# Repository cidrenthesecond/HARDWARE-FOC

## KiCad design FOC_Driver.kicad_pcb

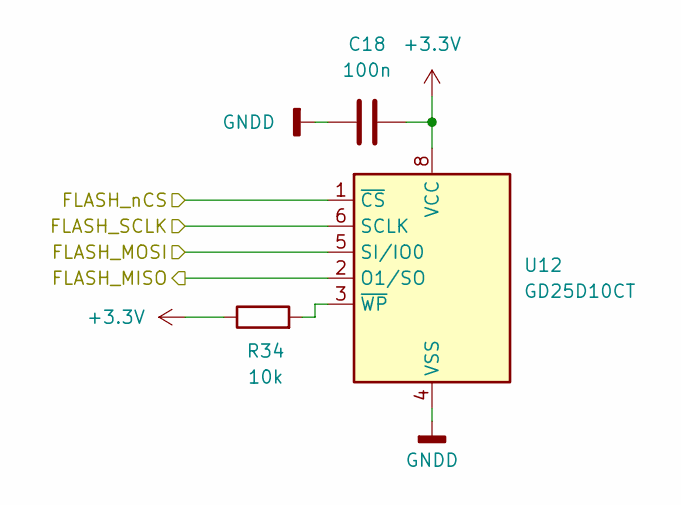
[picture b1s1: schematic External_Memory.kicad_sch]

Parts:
C18: 100n; C_0805_Private
R34: 10k; R_0805_Private
U12: GD25D10CT; JEITA_SOIC-8_3.9x4.9mm_P1.27mm

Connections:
+3.3V: C18.1, R34.1, U12.8 (VCC); also elsewhere on the board
/External_Memory/FLASH_MISO: U12.2 (O1/SO); also elsewhere on the board
/External_Memory/FLASH_MOSI: U12.5 (SI/IO0); also elsewhere on the board
/External_Memory/FLASH_SCLK: U12.6 (SCLK); also elsewhere on the board
/External_Memory/FLASH_nCS: U12.1 (~CS); also elsewhere on the board
GNDD: C18.2, U12.4 (VSS); also elsewhere on the board
unnamed: R34.2, U12.3 (~WP)

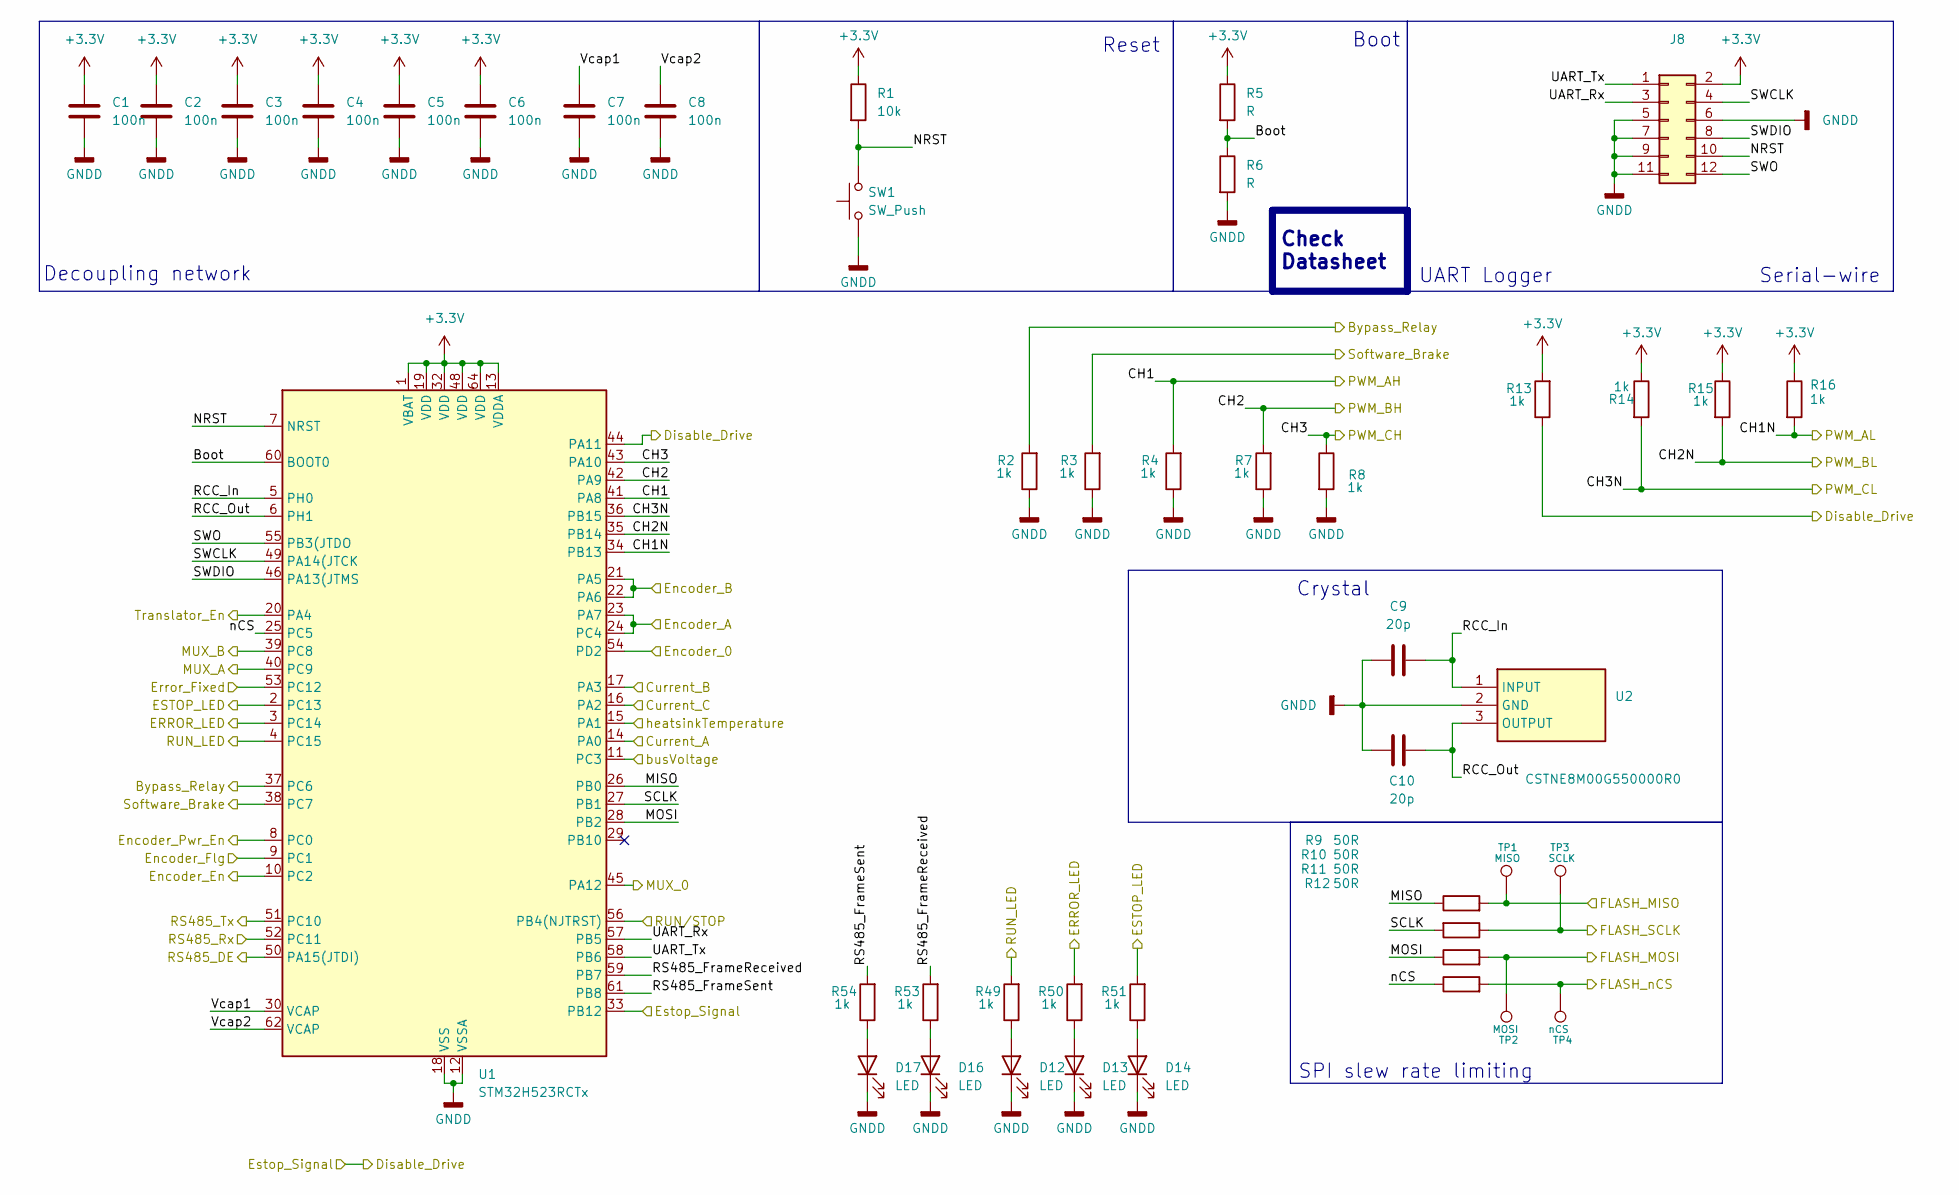
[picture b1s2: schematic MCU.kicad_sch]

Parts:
C1, C2, C3, C4, C5, C6, C7, C8: 100n; C_0805_Private
C9, C10: 20p; C_0805_Private
D12, D13, D14, D16, D17: LED; LED_0805_Private
J8: Conn_02x06_Odd_Even; PinHeader_2x06_P2.54mm_Vertical
R1: 10k; R_0805_Private
R2, R3, R4, R7, R8, R13, R14, R15, R16, R49, R50, R51, R53, R54: 1k; R_0805_Private
R5, R6: R; R_0805_Private
R9, R10, R11, R12: 50R; R_0805_Private
SW1: SW_Push; SW_PUSH_6mm_H5mm
TP1: MISO; TestPoint_Pad_D1.0mm
TP2: MOSI; TestPoint_Pad_D1.0mm
TP3: SCLK; TestPoint_Pad_D1.0mm
TP4: nCS; TestPoint_Pad_D1.0mm
U1: STM32H523RCTx; LQFP-64_10x10mm_P0.5mm
U2: CSTNE8M00G550000R0; CSTNE16M0V530000R0; Manufacturer_Part_Number CSTNE8M00G550000R0

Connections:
+3.3V: C1.1, C2.1, C3.1, C4.1, C5.1, C6.1, J8.2, R1.1, R5.1, R13.2, R14.1, R15.1, R16.1, U1.1 (VBAT), U1.13 (VDDA), U1.19 (VDD), U1.32 (VDD), U1.48 (VDD), U1.64 (VDD); also elsewhere on the board
/Connectors/BypassRelay: R2.2, U1.37 (PC6); also elsewhere on the board
/Connectors/Current_A: U1.14 (PA0); also elsewhere on the board
/Connectors/Current_B: U1.17 (PA3); also elsewhere on the board
/Connectors/Current_C: U1.16 (PA2); also elsewhere on the board
/Connectors/Disable_Drive: R13.1, U1.33 (PB12), U1.44 (PA11); also elsewhere on the board
/Connectors/SoftwareBrake: R3.2, U1.38 (PC7); also elsewhere on the board
/Connectors/busVoltage: U1.11 (PC3); also elsewhere on the board
/Connectors/heatsinkTemperature: U1.15 (PA1); also elsewhere on the board
/Encoder/Encoder_0: U1.54 (PD2); also elsewhere on the board
/Encoder/Encoder_A: U1.23 (PA7), U1.24 (PC4); also elsewhere on the board
/Encoder/Encoder_B: U1.21 (PA5), U1.22 (PA6); also elsewhere on the board
/Encoder/Encoder_En: U1.10 (PC2); also elsewhere on the board
/Encoder/Encoder_Flg: U1.9 (PC1); also elsewhere on the board
/Encoder/Encoder_Pwr_En: U1.8 (PC0); also elsewhere on the board
/Encoder/MUX_0: U1.45 (PA12); also elsewhere on the board
/Encoder/MUX_A: U1.40 (PC9); also elsewhere on the board
/Encoder/MUX_B: U1.39 (PC8); also elsewhere on the board
/Encoder/Translator_En: U1.20 (PA4); also elsewhere on the board
/External_Memory/FLASH_MISO: R9.2, TP1.1 (1_1); also elsewhere on the board
/External_Memory/FLASH_MOSI: R11.2, TP2.1 (1_1); also elsewhere on the board
/External_Memory/FLASH_SCLK: R10.1, TP3.1 (1_1); also elsewhere on the board
/External_Memory/FLASH_nCS: R12.2, TP4.1 (1_1); also elsewhere on the board
/MCU/Boot: R5.2, R6.1, U1.60 (BOOT0)
/MCU/CH1: R4.2, U1.41 (PA8); also elsewhere on the board
/MCU/CH1N: R16.2, U1.34 (PB13); also elsewhere on the board
/MCU/CH2: R7.2, U1.42 (PA9); also elsewhere on the board
/MCU/CH2N: R15.2, U1.35 (PB14); also elsewhere on the board
/MCU/CH3: R8.1, U1.43 (PA10); also elsewhere on the board
/MCU/CH3N: R14.2, U1.36 (PB15); also elsewhere on the board
/MCU/ERROR_LED: R50.2, U1.3 (PC14); also elsewhere on the board
/MCU/ESTOP_LED: R51.2, U1.2 (PC13); also elsewhere on the board
/MCU/MISO: R9.1, U1.26 (PB0)
/MCU/MOSI: R11.1, U1.28 (PB2)
/MCU/NRST: J8.10, R1.2, SW1.2, U1.7 (NRST)
/MCU/RCC_In: C9.2, U1.5 (PH0), U2.1 (INPUT)
/MCU/RCC_Out: C10.1, U1.6 (PH1), U2.3 (OUTPUT)
/MCU/RS485_DE: U1.50 (PA15(JTDI)); also elsewhere on the board
/MCU/RS485_FrameReceived: R53.2, U1.59 (PB7)
/MCU/RS485_FrameSent: R54.2, U1.61 (PB8)
/MCU/RS485_Rx: U1.52 (PC11); also elsewhere on the board
/MCU/RS485_Tx: U1.51 (PC10); also elsewhere on the board
/MCU/RUN_LED: R49.2, U1.4 (PC15); also elsewhere on the board
/MCU/SCLK: R10.2, U1.27 (PB1)
/MCU/SWCLK: J8.4, U1.49 (PA14(JTCK)
/MCU/SWDIO: J8.8, U1.46 (PA13(JTMS)
/MCU/SWO: J8.12, U1.55 (PB3(JTDO)
/MCU/UART_Rx: J8.3, U1.57 (PB5)
/MCU/UART_Tx: J8.1, U1.58 (PB6)
/MCU/Vcap1: C7.1, U1.30 (VCAP)
/MCU/Vcap2: C8.1, U1.62 (VCAP)
/MCU/nCS: R12.1, U1.25 (PC5)
Error_Fixed: U1.53 (PC12); also elsewhere on the board
GNDD: C1.2, C2.2, C3.2, C4.2, C5.2, C6.2, C7.2, C8.2, C9.1, C10.2, D12.1 (K), D13.1 (K), D14.1 (K), D16.1 (K), D17.1 (K), J8.5, J8.6, J8.7, J8.9, J8.11, R2.1, R3.1, R4.1, R6.2, R7.1, R8.2, SW1.1, U1.12 (VSSA), U1.18 (VSS), U1.31 (VSS), U1.47 (VSS), U1.63 (VSS), U2.2 (GND); also elsewhere on the board
unnamed: D12.2 (A), R49.1
unnamed: D13.2 (A), R50.1
unnamed: D14.2 (A), R51.1
unnamed: D16.2 (A), R53.1
unnamed: D17.2 (A), R54.1
RUN/STOP: U1.56 (PB4(NJTRST)); also elsewhere on the board

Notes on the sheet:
Crystal
SPI slew rate limiting
Check Datasheet
Decoupling network
Boot
UART Logger
Reset
Serial-wire

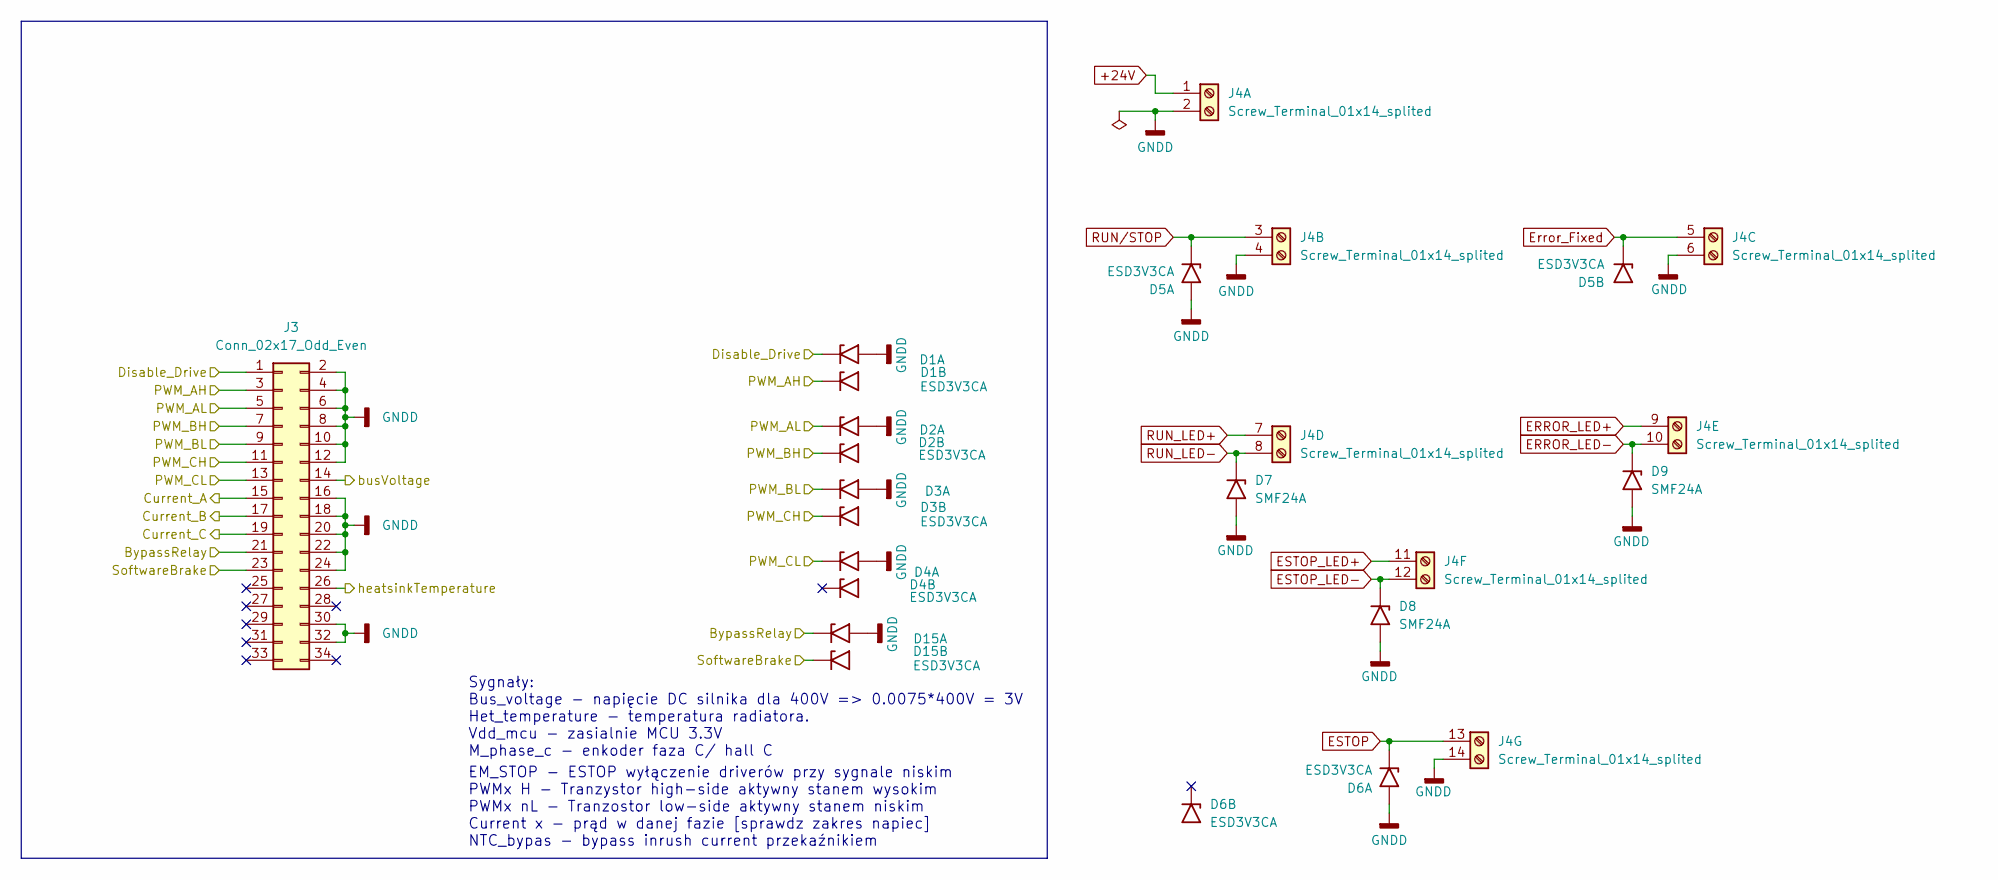
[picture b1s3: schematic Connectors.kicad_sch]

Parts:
D1, D2, D3, D4, D5, D6, D15: ESD3V3CA; SOT-23
D7, D8, D9: SMF24A; D_SMF_Private
J3: Conn_02x17_Odd_Even; IDC-Header_2x17_P2.54mm_Vertical
J4: Screw_Terminal_01x14_splited; TerminalBlock_Xinya_XY308-2.54-14P_1x14_P2.54mm_Horizontal

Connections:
/Connectors/BypassRelay: D15.1 (A1), J3.21; also elsewhere on the board
/Connectors/Current_A: J3.15; also elsewhere on the board
/Connectors/Current_B: J3.17; also elsewhere on the board
/Connectors/Current_C: J3.19; also elsewhere on the board
/Connectors/Disable_Drive: D1.1 (A1), J3.1; also elsewhere on the board
/Connectors/SoftwareBrake: D15.2 (A1), J3.23; also elsewhere on the board
/Connectors/busVoltage: J3.14; also elsewhere on the board
/Connectors/heatsinkTemperature: J3.26; also elsewhere on the board
/MCU/CH1: D1.2 (A1), J3.3; also elsewhere on the board
/MCU/CH1N: D2.1 (A1), J3.5; also elsewhere on the board
/MCU/CH2: D2.2 (A1), J3.7; also elsewhere on the board
/MCU/CH2N: D3.1 (A1), J3.9; also elsewhere on the board
/MCU/CH3: D3.2 (A1), J3.11; also elsewhere on the board
/MCU/CH3N: D4.1 (A1), J3.13; also elsewhere on the board
ERROR_LED-: D9.1 (A1), J4.10 (1); also elsewhere on the board
ESTOP: D6.1 (A1), J4.13 (Pin_1); also elsewhere on the board
ESTOP_LED-: D8.1 (A1), J4.12 (10); also elsewhere on the board
Error_Fixed: D5.2 (A1), J4.5 (Pin_1); also elsewhere on the board
GNDD: D1.3, D2.3, D3.3, D4.3, D5.3, D6.3, D7.2 (A2), D8.2 (A2), D9.2 (A2), D15.3, J3.2, J3.4, J3.6, J3.8, J3.10, J3.12, J3.16, J3.18, J3.20, J3.22, J3.24, J3.30, J3.32, J4.2, J4.4 (Pin_2), J4.6 (Pin_2), J4.14 (Pin_2); also elsewhere on the board
RUN_LED-: D7.1 (A1), J4.8 (Pin_2); also elsewhere on the board
RUN/STOP: D5.1 (A1), J4.3 (Pin_1); also elsewhere on the board

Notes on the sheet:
EM_STOP - ESTOP wyłączenie driverów przy sygnale niskim PWMx H - Tranzystor high-side aktywny stanem wysokim PWMx nL - Tranzostor low-side aktywny stanem niskim Current x - prąd w danej fazie [sprawdz zakres napiec] NTC_bypas - bypass inrush current przekaźnikiem
Sygnały: Bus_voltage - napięcie DC silnika dla 400V => 0.0075*400V = 3V Het_temperature - temperatura radiatora. Vdd_mcu - zasialnie MCU 3.3V M_phase_c - enkoder faza C/ hall C

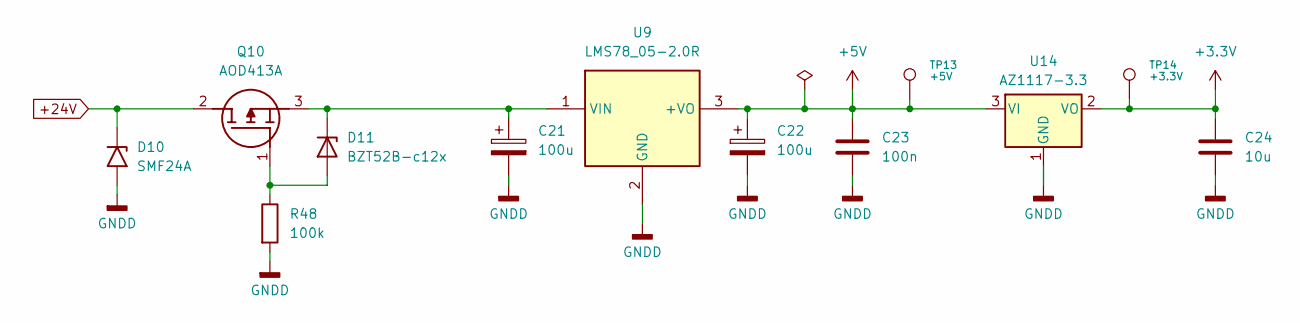
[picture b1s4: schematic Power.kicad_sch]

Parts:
C21, C22: 100u; CP_Radial_D8.0mm_P3.50mm
C23: 100n; C_0805_Private
C24: 10u; C_0805_Private
D10: SMF24A; D_SMF_Private
D11: BZT52B-c12x; D_SOD-123F_Private
Q10: AOD413A; Manufacturer_Part_Number AOD413A
R48: 100k; R_0805_Private
TP13: +5V; TestPoint_Pad_D1.0mm
TP14: +3.3V; TestPoint_Pad_D1.0mm
U9: LMS78_05-2.0R; LMS78_0520R; Manufacturer_Part_Number LMS78_05-2.0R
U14: AZ1117-3.3; SOT-223-3_TabPin2

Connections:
+3.3V: C24.2, TP14.1 (1_1), U14.2 (VO); also elsewhere on the board
+5V: C22.1, C23.2, TP13.1 (1_1), U9.3 (+VO), U14.3 (VI); also elsewhere on the board
GNDD: C21.2, C22.2, C23.1, C24.1, D10.2 (A2), R48.2, U9.2 (GND), U14.1 (GND); also elsewhere on the board
unnamed: D11.2 (A), Q10.1 (G), R48.1
unnamed: C21.1, D11.1 (K), Q10.3 (S), U9.1 (VIN)

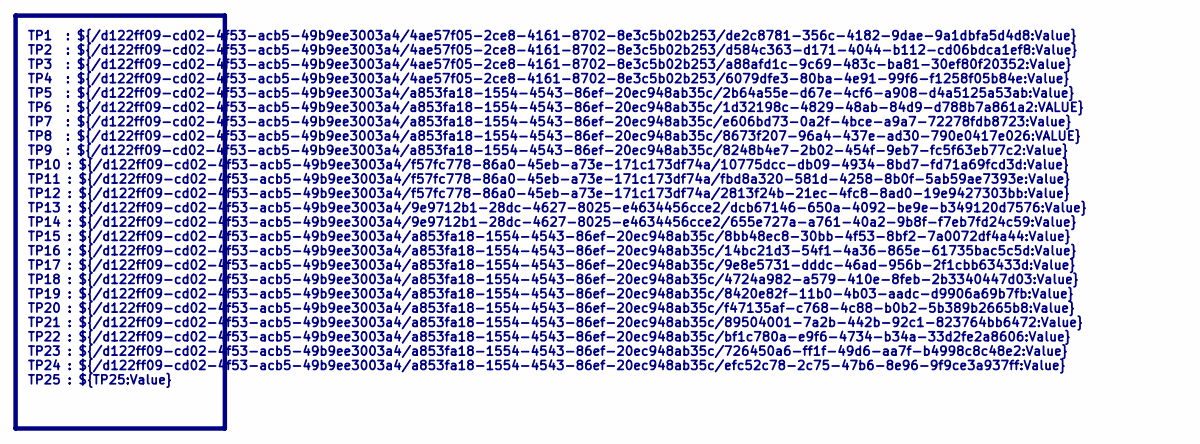
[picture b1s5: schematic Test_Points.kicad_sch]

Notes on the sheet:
TP1 : ${/d122ff09-cd02-4f53-acb5-49b9ee3003a4/4ae57f05-2ce8-4161-8702-8e3c5b02b253/de2c8781-356c-4182-9dae-9a1dbfa5d4d8:Value} TP2 : ${/d122ff09-cd02-4f53-acb5-49b9ee3003a4/4ae57f05-2ce8-4161-8702-8e3c5b02b253/d584c363-d171-4044-b112-cd06bdca1ef8:Value} TP3 : ${/d122ff09-cd02-4f53-acb5-49b9ee3003a4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

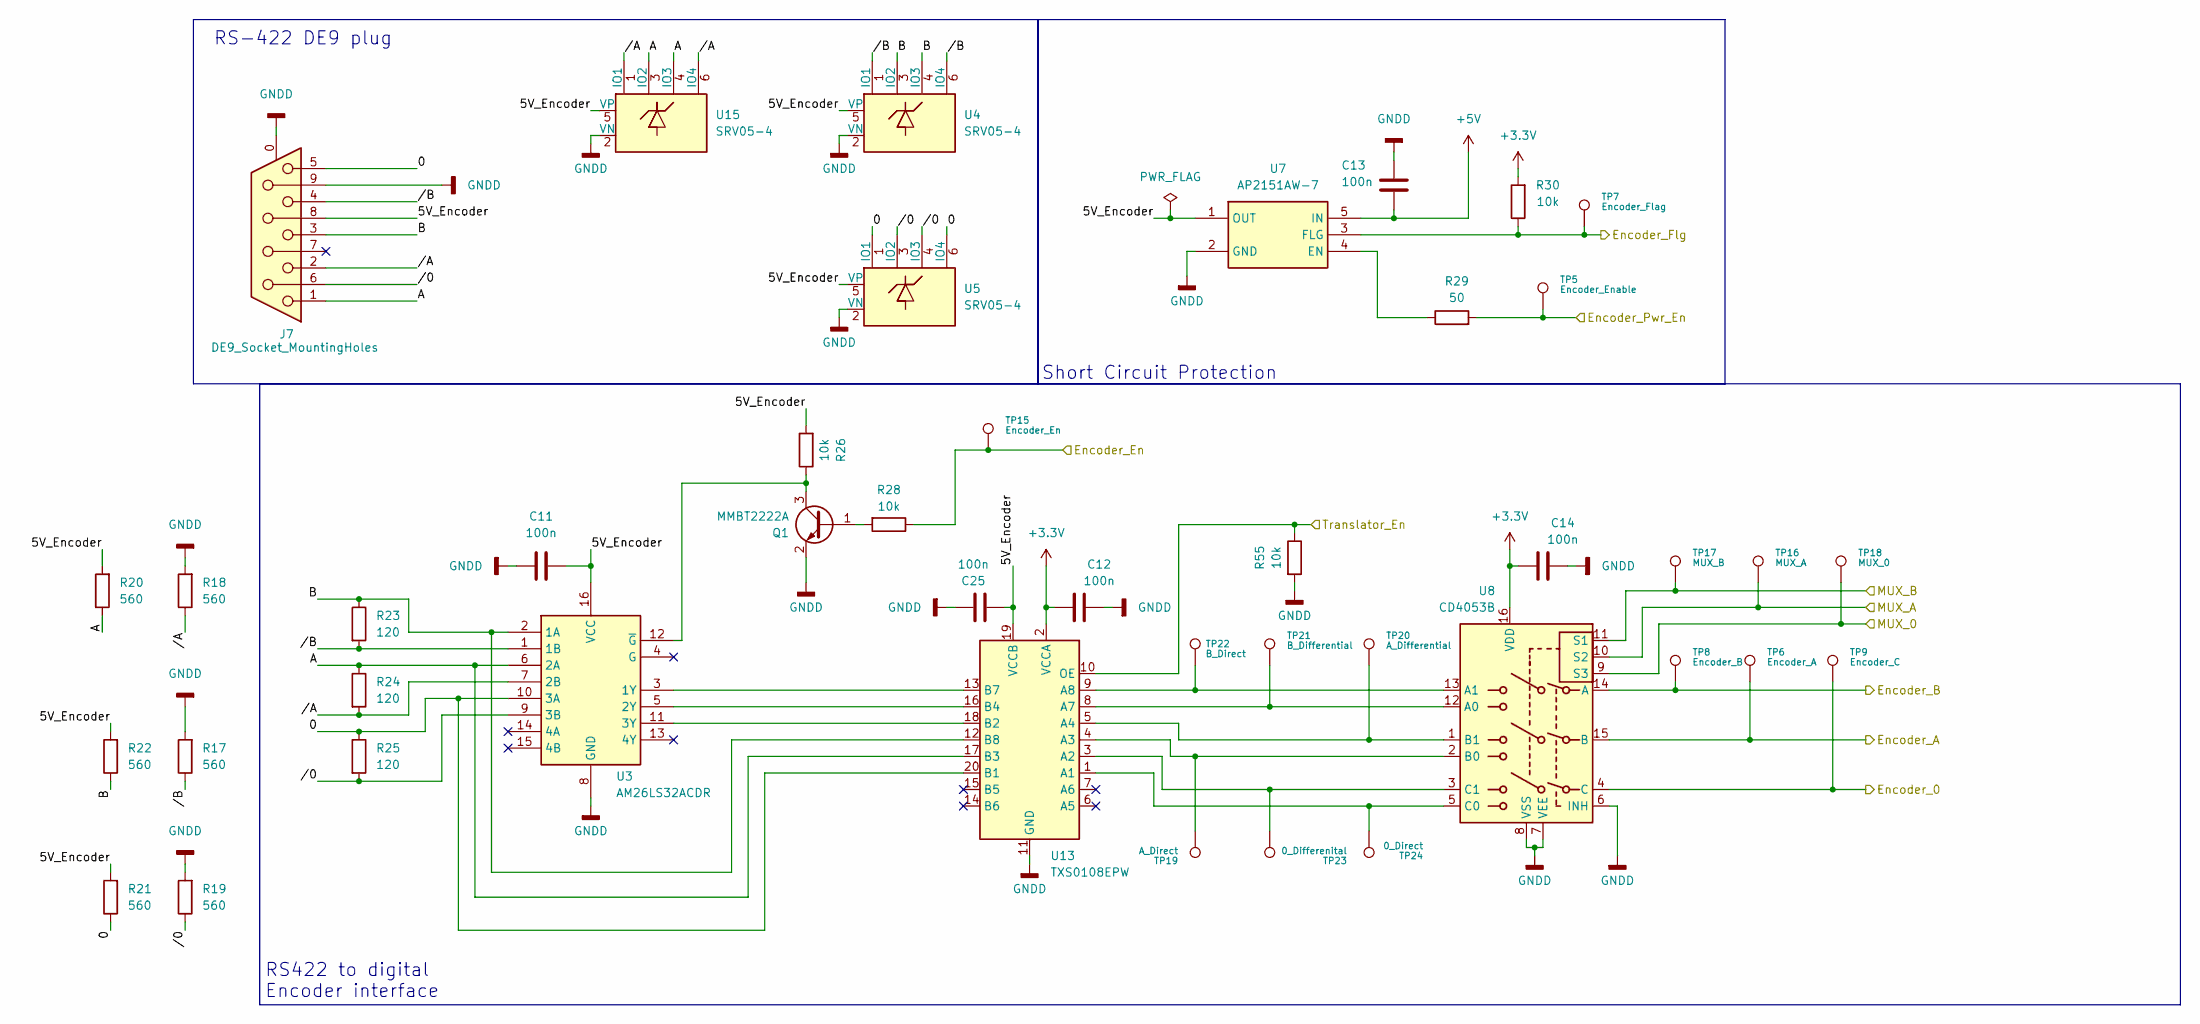
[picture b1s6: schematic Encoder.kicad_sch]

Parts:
C11, C12, C13, C14, C25: 100n; C_0805_Private
J7: DE9_Socket_MountingHoles; DSUB-9_Socket_Horizontal_P2.77x2.84mm_EdgePinOffset4.94mm_H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
Q1: MMBT2222A; SOT-23
R17, R18, R19, R20, R21, R22: 560; R_0805_Private
R23, R24, R25: 120; R_0805_Private
R26, R28, R30, R55: 10k; R_0805_Private
R29: 50; R_0805_Private
TP5: Encoder_Enable; TestPoint_Pad_D1.0mm
TP6: Encoder_A; TestPoint_Pad_D1.0mm
TP7: Encoder_Flag; TestPoint_Pad_D1.0mm
TP8: Encoder_B; TestPoint_Pad_D1.0mm
TP9: Encoder_C; TestPoint_Pad_D1.0mm
TP15: Encoder_En; TestPoint_Pad_D1.0mm
TP16: MUX_A; TestPoint_Pad_D1.0mm
TP17: MUX_B; TestPoint_Pad_D1.0mm
TP18: MUX_0; TestPoint_Pad_D1.0mm
TP19: A_Direct; TestPoint_Pad_D1.0mm
TP20: A_Differential; TestPoint_Pad_D1.0mm
TP21: B_Differential; TestPoint_Pad_D1.0mm
TP22: B_Direct; TestPoint_Pad_D1.0mm
TP23: 0_Differenital; TestPoint_Pad_D1.0mm
TP24: 0_Direct; TestPoint_Pad_D1.0mm
U3: AM26LS32ACDR; SOIC127P600X175-16N; Manufacturer_Part_Number AM26LS32ACDR
U4, U5, U15: SRV05-4; SOT-23-6
U7: AP2151AW-7; SOT95P285X140-5N; Manufacturer_Part_Number AP2151AW-7
U8: CD4053B; SOIC-16_3.9x9.9mm_P1.27mm
U13: TXS0108EPW; TSSOP-20_4.4x6.5mm_P0.65mm

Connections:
+3.3V: C12.1, C14.1, R30.2, U8.16 (VDD), U13.2 (VCCA); also elsewhere on the board
+5V: C13.2, U7.5 (IN); also elsewhere on the board
/Encoder/0: J7.5, R21.1, R25.1, U3.10 (3A), U5.1 (IO1), U5.6 (IO4), U13.20 (B1)
/Encoder/5V_Encoder: C11.2, C25.1, J7.8, R20.2, R21.2, R22.2, R26.2, U3.16 (VCC), U4.5 (VP), U5.5 (VP), U7.1 (OUT), U13.19 (VCCB), U15.5 (VP)
/Encoder/A: J7.1, R20.1, R24.1, U3.6 (2A), U13.17 (B3), U15.3 (IO2), U15.4 (IO3)
/Encoder/B: J7.3, R22.1, R23.1, U3.2 (1A), U4.3 (IO2), U4.4 (IO3), U13.12 (B8)
/Encoder/Encoder_0: TP9.1 (1_1), U8.4 (C); also elsewhere on the board
/Encoder/Encoder_A: TP6.1 (1_1), U8.15 (B); also elsewhere on the board
/Encoder/Encoder_B: TP8.1 (1_1), U8.14 (A); also elsewhere on the board
/Encoder/Encoder_En: R28.1, TP15.1 (1_1); also elsewhere on the board
/Encoder/Encoder_Flg: R30.1, TP7.1 (1_1), U7.3 (FLG); also elsewhere on the board
/Encoder/Encoder_Pwr_En: R29.2, TP5.1 (1_1); also elsewhere on the board
/Encoder/MUX_0: TP18.1 (1_1), U8.9 (S3); also elsewhere on the board
/Encoder/MUX_A: TP16.1 (1_1), U8.10 (S2); also elsewhere on the board
/Encoder/MUX_B: TP17.1 (1_1), U8.11 (S1); also elsewhere on the board
/Encoder/Translator_En: R55.1, U13.10 (OE); also elsewhere on the board
/Encoder//0: J7.6, R19.1, R25.2, U3.9 (3B), U5.3 (IO2), U5.4 (IO3)
/Encoder//A: J7.2, R18.1, R24.2, U3.7 (2B), U15.1 (IO1), U15.6 (IO4)
/Encoder//B: J7.4, R17.1, R23.2, U3.1 (1B), U4.1 (IO1), U4.6 (IO4)
GNDD: C11.1, C12.2, C13.1, C14.2, C25.2, J7.0 (PAD), J7.9, J7.SH, Q1.2 (E), R17.2, R18.2, R19.2, R55.2, U3.8 (GND), U4.2 (VN), U5.2 (VN), U7.2 (GND), U8.6 (INH), U8.7 (VEE), U8.8 (VSS), U13.11 (GND), U15.2 (VN); also elsewhere on the board
unnamed: Q1.1 (B), R28.2
unnamed: Q1.3 (C), R26.1, U3.12 (~G)
unnamed: R29.1, U7.4 (EN)
unnamed: TP24.1 (1_1), U8.5 (C0), U13.1 (A1)
unnamed: TP23.1 (1_1), U8.3 (C1), U13.3 (A2)
unnamed: TP19.1 (1_1), U8.2 (B0), U13.4 (A3)
unnamed: TP20.1 (1_1), U8.1 (B1), U13.5 (A4)
unnamed: TP21.1 (1_1), U8.12 (A0), U13.8 (A7)
unnamed: TP22.1 (1_1), U8.13 (A1), U13.9 (A8)
unnamed: U3.11 (3Y), U13.18 (B2)
unnamed: U3.5 (2Y), U13.16 (B4)
unnamed: U3.3 (1Y), U13.13 (B7)

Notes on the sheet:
RS422 to digital Encoder interface
Short Circuit Protection
RS-422 DE9 plug

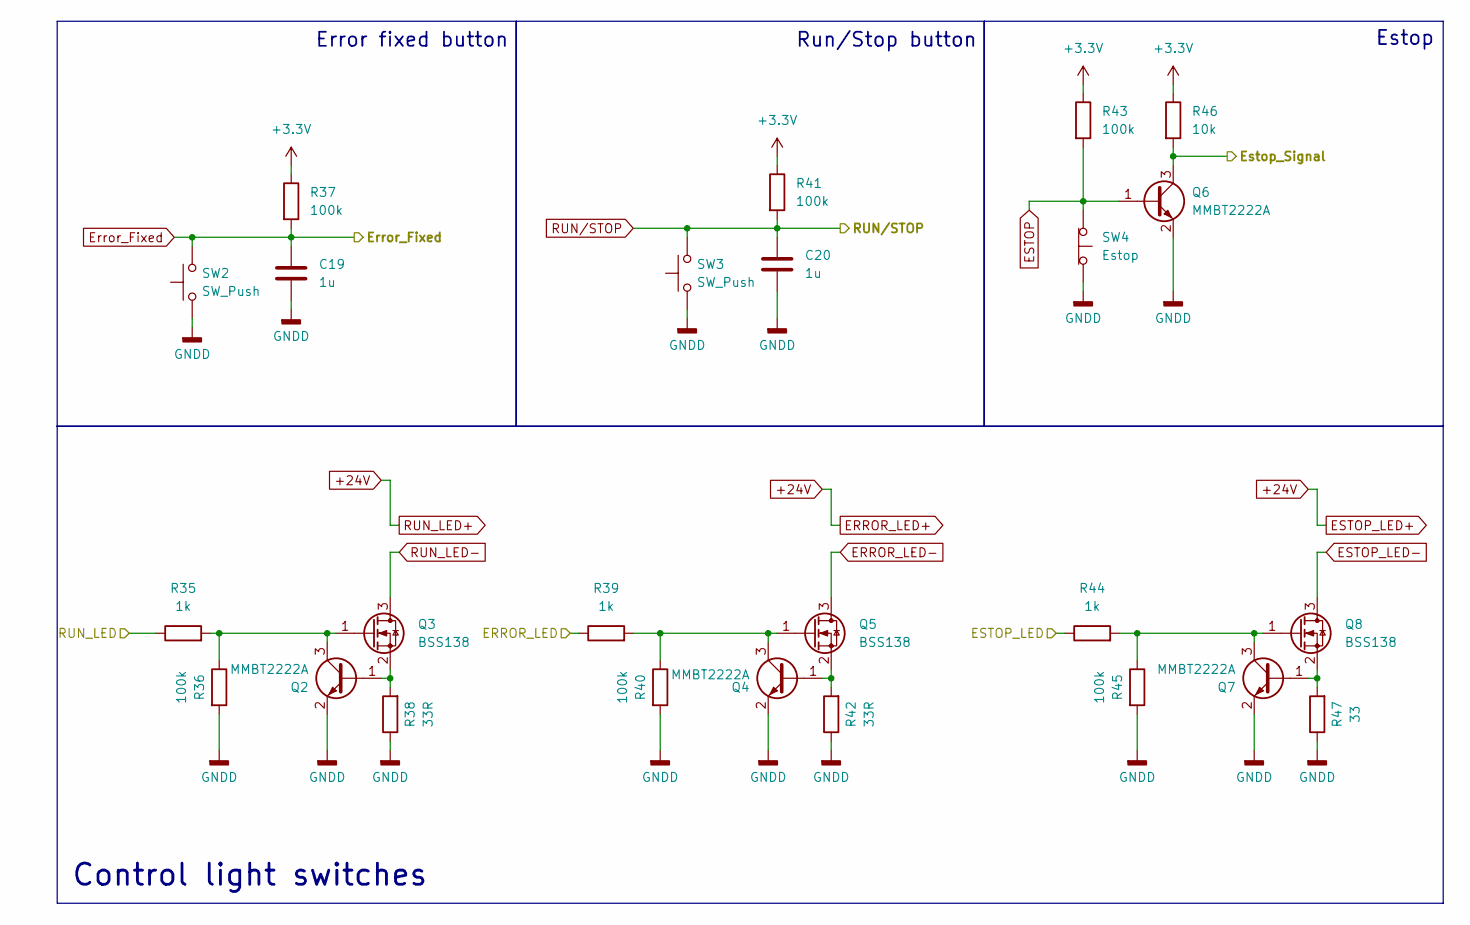
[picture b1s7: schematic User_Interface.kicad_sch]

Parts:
C19, C20: 1u; C_0805_Private
Q2, Q4, Q6, Q7: MMBT2222A; SOT-23
Q3, Q5, Q8: BSS138; SOT-23
R35, R39, R44: 1k; R_0805_Private
R36, R37, R40, R41, R43, R45: 100k; R_0805_Private
R38, R42: 33R; R_0805_Private
R46: 10k; R_0805_Private
R47: 33; R_0805_Private
SW2, SW3: SW_Push; SW_PUSH_6mm_H5mm
SW4: Estop

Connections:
+3.3V: R37.1, R41.1, R43.1, R46.1; also elsewhere on the board
/Connectors/Disable_Drive: Q6.3 (C), R46.2; also elsewhere on the board
/MCU/ERROR_LED: R39.1; also elsewhere on the board
/MCU/ESTOP_LED: R44.1; also elsewhere on the board
/MCU/RUN_LED: R35.1; also elsewhere on the board
ERROR_LED-: Q5.3 (D); also elsewhere on the board
ESTOP: Q6.1 (B), R43.2, SW4.1 (A); also elsewhere on the board
ESTOP_LED-: Q8.3 (D); also elsewhere on the board
Error_Fixed: C19.1, R37.2, SW2.2; also elsewhere on the board
GNDD: C19.2, C20.2, Q2.2 (E), Q4.2 (E), Q6.2 (E), Q7.2 (E), R36.2, R38.1, R40.2, R42.1, R45.2, R47.1, SW2.1, SW3.1, SW4.2 (B); also elsewhere on the board
unnamed: Q2.1 (B), Q3.2 (S), R38.2
unnamed: Q2.3 (C), Q3.1 (G), R35.2, R36.1
unnamed: Q4.1 (B), Q5.2 (S), R42.2
unnamed: Q4.3 (C), Q5.1 (G), R39.2, R40.1
unnamed: Q7.1 (B), Q8.2 (S), R47.2
unnamed: Q7.3 (C), Q8.1 (G), R44.2, R45.1
RUN_LED-: Q3.3 (D); also elsewhere on the board
RUN/STOP: C20.1, R41.2, SW3.2; also elsewhere on the board

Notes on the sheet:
Control light switches
Run/Stop button
Estop
Error fixed button

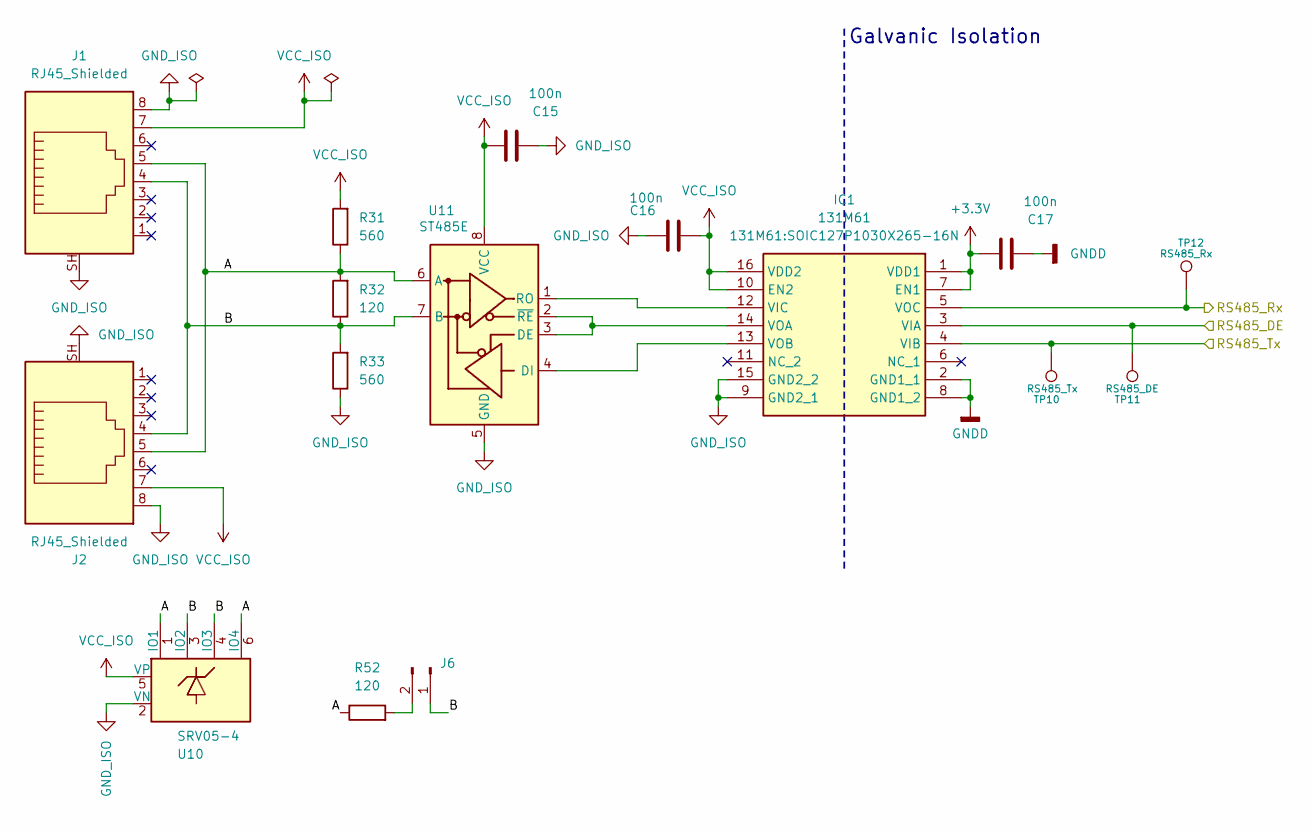
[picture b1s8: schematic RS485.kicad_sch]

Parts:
C15, C16, C17: 100n; C_0805_Private
IC1: 131M61; SOIC127P1030X265-16N; Manufacturer_Part_Number Π131M61
J1, J2: RJ45_Shielded; RJ45_Private
J6: Conn_01x02_Pin; PinHeader_1x02_P2.54mm_Vertical
R31, R33: 560; R_0805_Private
R32, R52: 120; R_0805_Private
TP10: RS485_Tx; TestPoint_Pad_D1.0mm
TP11: RS485_DE; TestPoint_Pad_D1.0mm
TP12: RS485_Rx; TestPoint_Pad_D1.0mm
U10: SRV05-4; SOT-23-6
U11: ST485E; SOIC-8_3.9x4.9mm_P1.27mm

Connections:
+3.3V: C17.2, IC1.1 (VDD1), IC1.7 (EN1); also elsewhere on the board
/MCU/RS485_DE: IC1.3 (VIA), TP11.1 (1_1); also elsewhere on the board
/MCU/RS485_Rx: IC1.5 (VOC), TP12.1 (1_1); also elsewhere on the board
/MCU/RS485_Tx: IC1.4 (VIB), TP10.1 (1_1); also elsewhere on the board
/RS485/A: J1.5, J2.5, R31.1, R32.2, R52.1, U10.1 (IO1), U10.6 (IO4), U11.6 (A)
/RS485/B: J1.4, J2.4, J6.1, R32.1, R33.2, U10.3 (IO2), U10.4 (IO3), U11.7 (B)
GNDD: C17.1, IC1.2 (GND1_1), IC1.8 (GND1_2); also elsewhere on the board
GND_ISO: C15.1, C16.2, IC1.9 (GND2_1), IC1.15 (GND2_2), J1.8, J1.SH, J2.8, J2.SH, R33.1, U10.2 (VN), U11.5 (GND)
unnamed: IC1.12 (VIC), U11.1 (RO)
unnamed: IC1.14 (VOA), U11.2 (~RE), U11.3 (DE)
unnamed: IC1.13 (VOB), U11.4 (DI)
unnamed: J6.2, R52.2
VCC_ISO: C15.2, C16.1, IC1.10 (EN2), IC1.16 (VDD2), J1.7, J2.7, R31.2, U10.5 (VP), U11.8 (VCC)

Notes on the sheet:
Galvanic Isolation

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
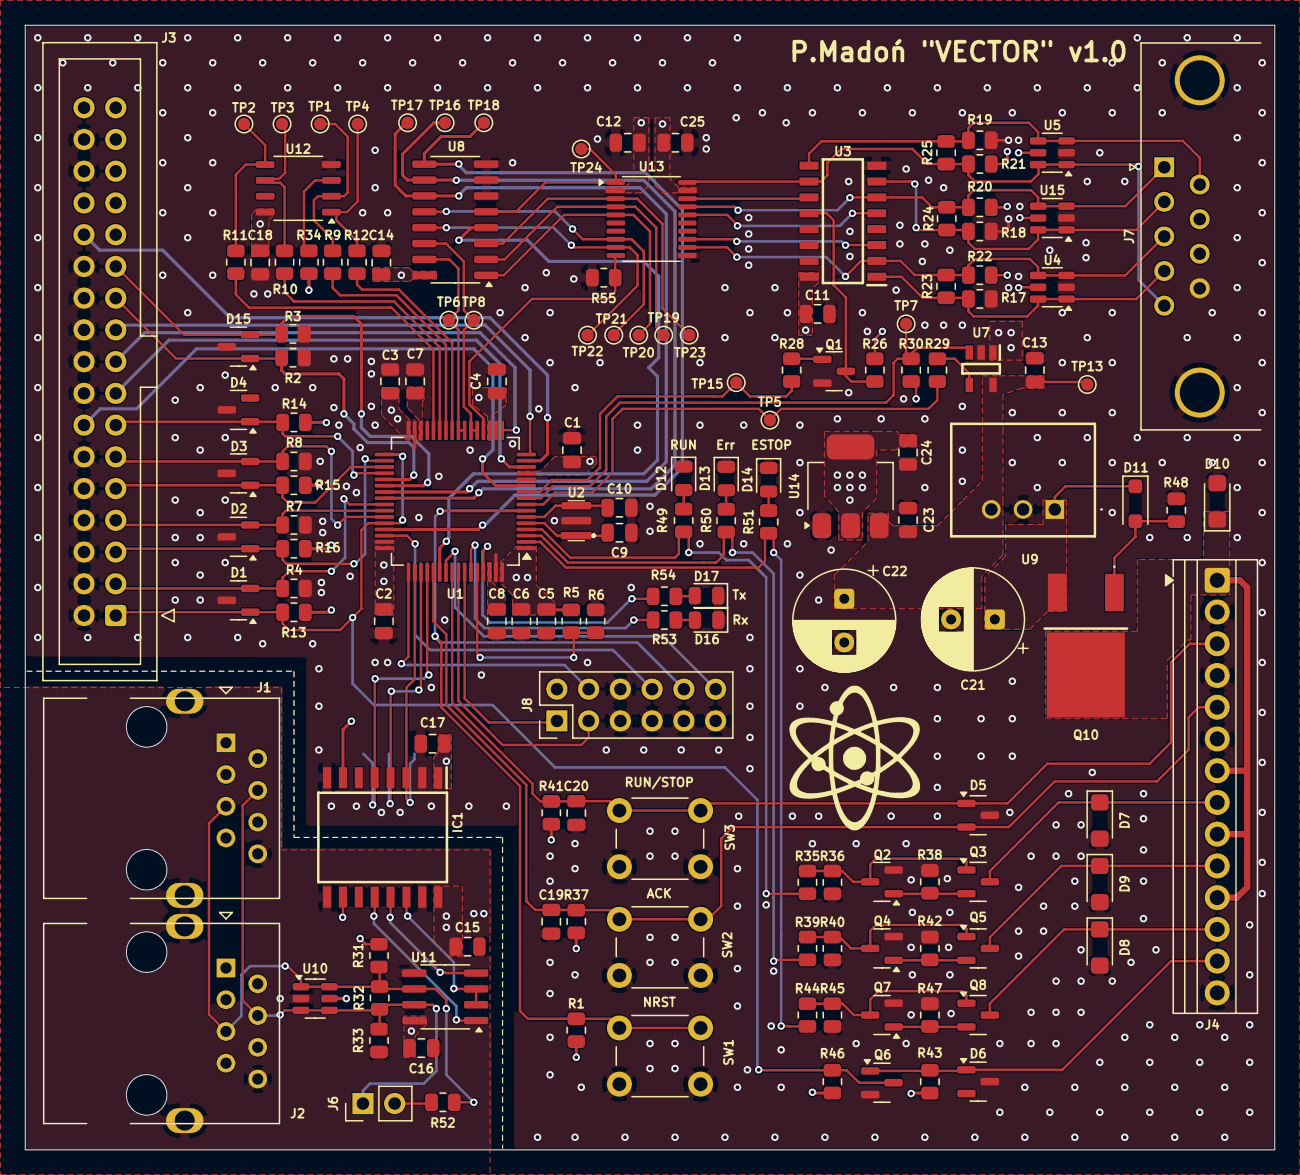
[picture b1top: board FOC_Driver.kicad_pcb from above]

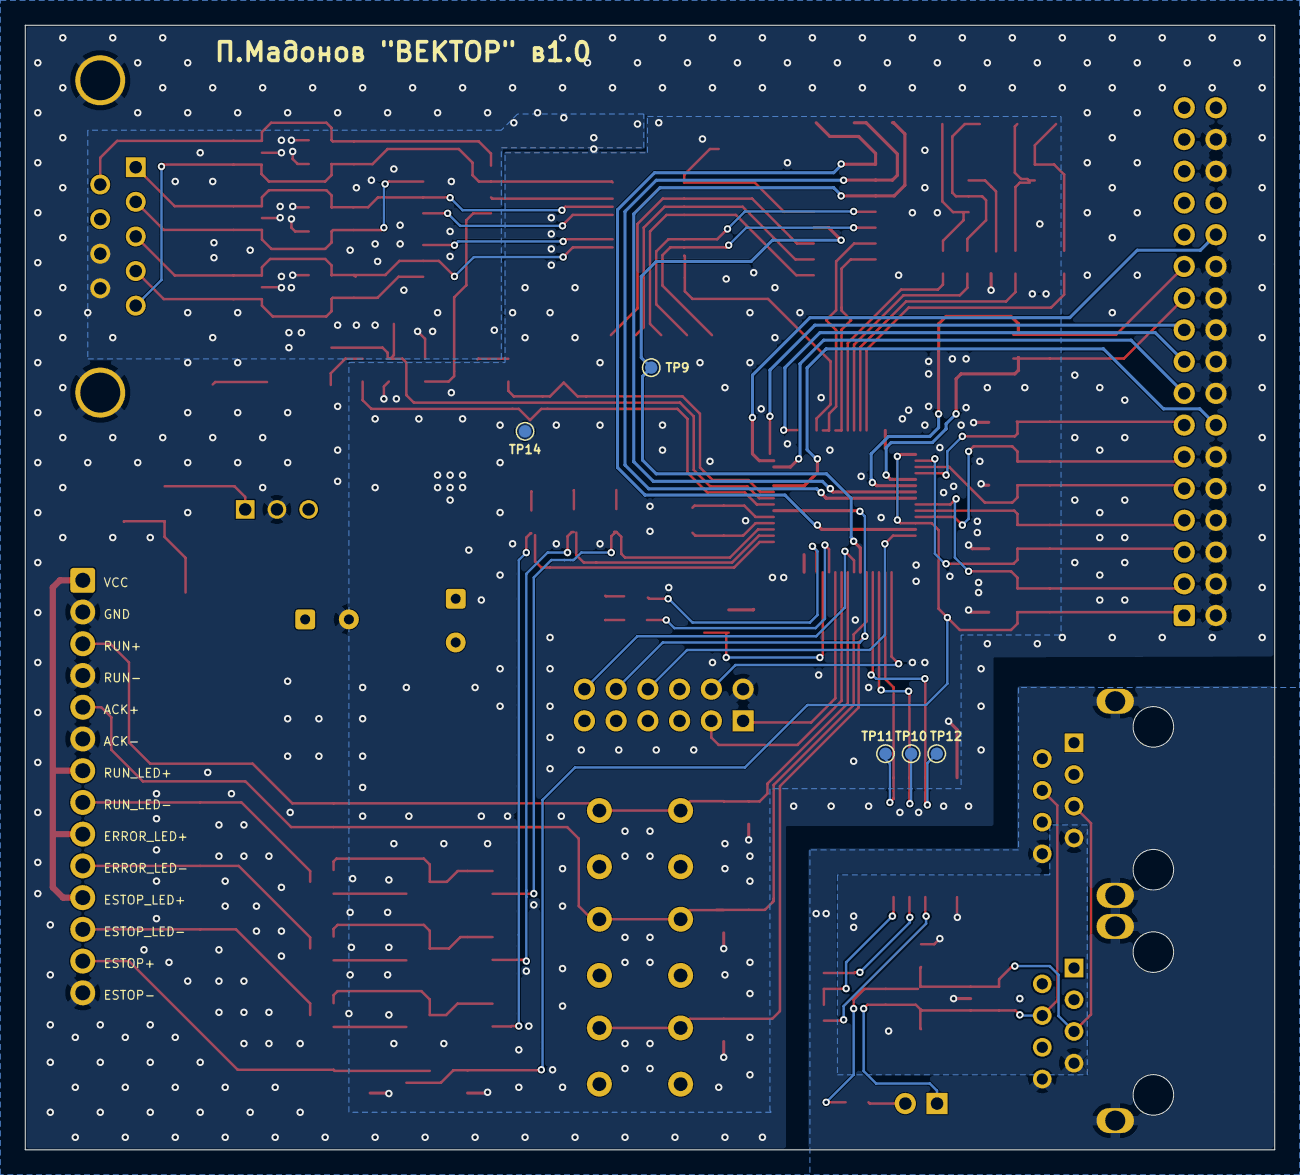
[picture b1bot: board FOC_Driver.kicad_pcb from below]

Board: 4 copper layers, 100.0 x 90.0 mm, 154 parts (5 on the bottom side), 102 nets.

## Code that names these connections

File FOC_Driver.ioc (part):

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Mcu.Name=STM32H523RCTx
Mcu.Package=LQFP64
Mcu.UserName=STM32H523RCTx
PA0.Signal=ADCx_INP0
PA1.Signal=ADCx_INP1
PA10.Signal=S_TIM1_CH3
PA11.GPIOParameters=GPIO_Label
PA11.GPIO_Label=Disable_Drive
PA11.Signal=GPIO_Output
PA13(JTMS/SWDIO).Mode=Trace_Asynchronous_SW
PA13(JTMS/SWDIO).Signal=DEBUG_JTMS-SWDIO
PA14(JTCK/SWCLK).Mode=Trace_Asynchronous_SW
PA14(JTCK/SWCLK).Signal=DEBUG_JTCK-SWCLK
PA15(JTDI).Mode=Hardware Flow Control (RS485)
PA15(JTDI).Signal=UART4_DE
PA2.Signal=ADCx_INP14
PA3.Signal=ADCx_INP15
PA5.Signal=S_TIM2_CH1
PA6.Signal=S_TIM3_CH1
PA7.Signal=S_TIM3_CH2
PA8.Signal=S_TIM1_CH1
PA9.Signal=S_TIM1_CH2
PB0.Mode=Full_Duplex_Master
PB0.Signal=SPI3_MISO
PB1.Mode=Full_Duplex_Master
PB1.Signal=SPI3_SCK
PB12.Mode=Activate-Break-Input
PB12.Signal=TIM1_BKIN
PB13.Mode=Output Compare1 CH1 CH1N
PB13.Signal=TIM1_CH1N
PB14.Mode=Output Compare2 CH2 CH2N
PB14.Signal=TIM1_CH2N
PB15.Mode=Output Compare3 CH3 CH3N
PB15.Signal=TIM1_CH3N
PB2.Mode=Full_Duplex_Master
PB2.Signal=SPI3_MOSI
PB3(JTDO/TRACESWO).Mode=Trace_Asynchronous_SW
PB3(JTDO/TRACESWO).Signal=DEBUG_JTDO-SWO
PB5.Mode=Asynchronous
PB5.Signal=UART5_RX
PB6.Mode=Asynchronous
PB6.Signal=UART5_TX
PC0.GPIOParameters=GPIO_Label
PC0.GPIO_Label=Encoder_Pwr_Enable
PC0.Signal=GPIO_Output
PC1.GPIOParameters=GPIO_Label
PC1.GPIO_Label=Encoder_Flag
PC1.Signal=GPIO_Input
PC10.Mode=Asynchronous
PC10.Signal=UART4_TX
PC11.Mode=Asynchronous
PC11.Signal=UART4_RX
PC13.GPIOParameters=GPIO_Label
PC13.GPIO_Label=ESTOP_LED
PC13.Signal=GPIO_Output
PC14-OSC32_IN(OSC32_IN).GPIOParameters=GPIO_Label
PC14-OSC32_IN(OSC32_IN).GPIO_Label=ERROR_LED
PC14-OSC32_IN(OSC32_IN).Signal=GPIO_Output
PC15-OSC32_OUT(OSC32_OUT).GPIOParameters=GPIO_Label
PC15-OSC32_OUT(OSC32_OUT).GPIO_Label=RUN_LED
PC15-OSC32_OUT(OSC32_OUT).Signal=GPIO_Output
PC2.GPIOParameters=GPIO_Label
PC2.GPIO_Label=Encoder_Enable
PC2.Signal=GPIO_Output
PC3.Signal=ADCx_INP13
PC4.Signal=S_TIM2_CH4
PC5.GPIOParameters=GPIO_Label
PC5.GPIO_Label=nCS
PC5.Signal=GPIO_Output
PC6.GPIOParameters=GPIO_Label
PC6.GPIO_Label=Software_brake
PC6.Signal=GPIO_Output
PC7.GPIOParameters=GPIO_Label
PC7.GPIO_Label=Bypass_Relay
PC7.Signal=GPIO_Output
PD2.Signal=S_TIM3_ETR
PH0-OSC_IN(PH0).Mode=HSE-External-Oscillator
PH0-OSC_IN(PH0).Signal=RCC_OSC_IN
PH1-OSC_OUT(PH1).Mode=HSE-External-Oscillator
PH1-OSC_OUT(PH1).Signal=RCC_OSC_OUT
RCC.HSE_VALUE=16000000
RCC.SYSCLKFreq_VALUE=250000000
RCC.SYSCLKSource=RCC_SYSCLKSOURCE_PLLCLK
board=custom
